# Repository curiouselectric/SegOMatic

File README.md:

# SegOMatic
Design files for a 7 segment LED DIY kit

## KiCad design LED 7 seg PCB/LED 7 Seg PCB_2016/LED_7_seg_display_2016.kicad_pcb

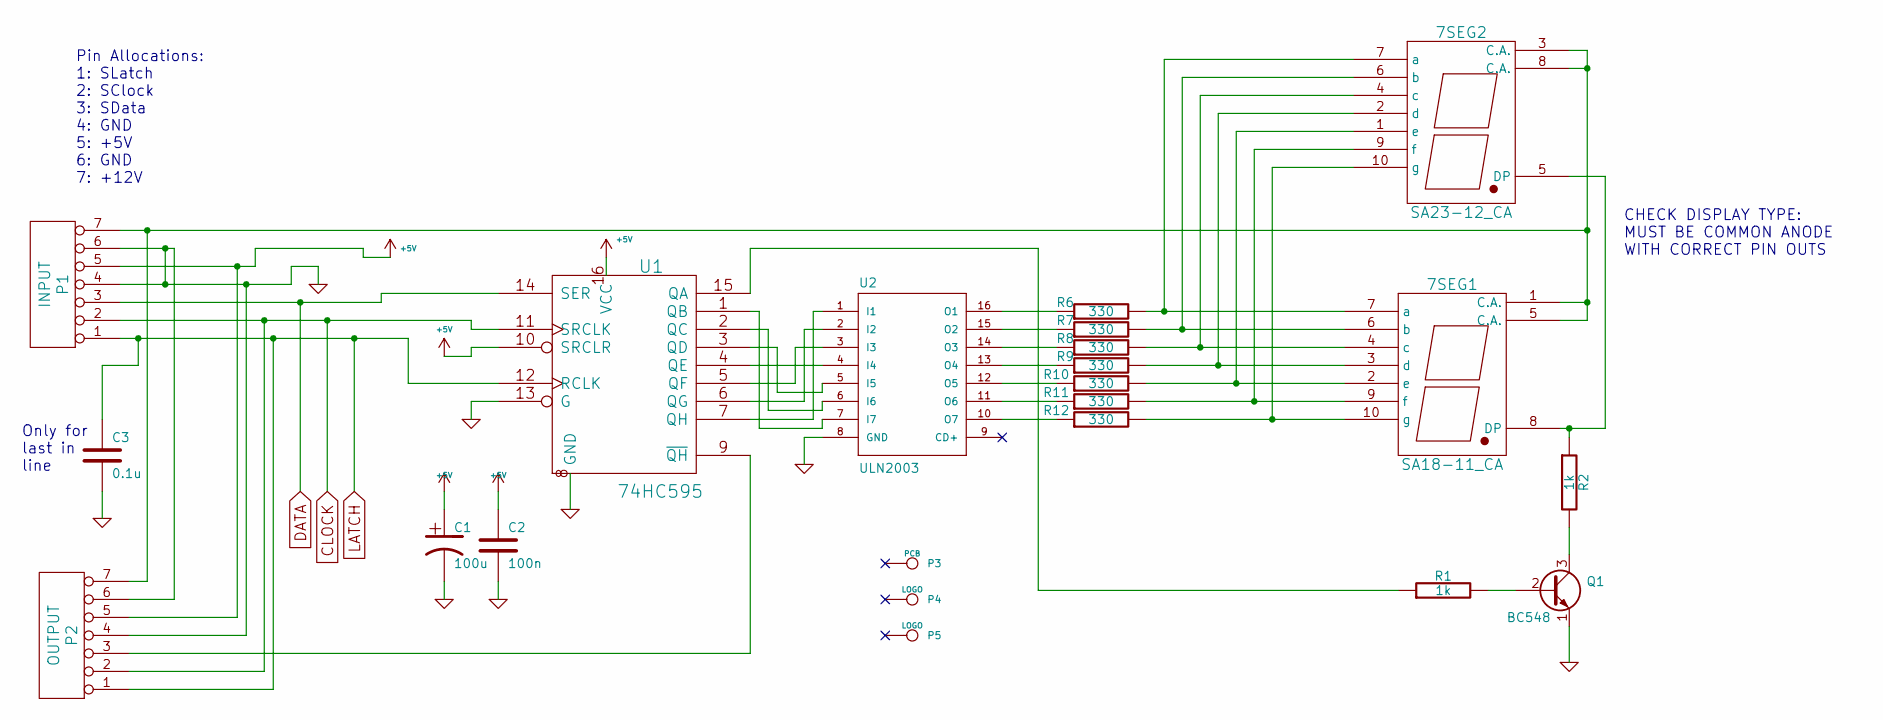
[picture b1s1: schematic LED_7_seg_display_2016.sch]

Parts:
7SEG1: SA18-11_CA; 7SEG_CA_SA18-11
7SEG2: SA23-12_CA; 7SEG_CC_2_3INCH
C1: 100u; C_Radial_D6.3_L11.2_P2.5
C2: 100n; C1_wide_lg_pad
C3: 0.1u; C1_wide_lg_pad
P1: INPUT; TH_SIL-7_large_pads
P2: OUTPUT; TH_SIL-7_large_pads
P3: PCB; PCB_40x85mm
P4: LOGO; CuriousElectric_globe_10mm
P5: LOGO; TCEC_Words_13mm
Q1: BC548; TH_TO92-EBC_large_pad
R1, R2: 1k; TH_Resistor_1
R6, R7, R8, R9, R10, R11, R12: 330; TH_Resistor_1
U1: 74HC595; TH_DIP-16__300_ELL
U2: ULN2003; TH_DIP-16__300_ELL

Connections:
+5V: C1.1, C2.1, P1.5, P2.5, U1.10 (SRCLR), U1.16 (VCC)
CLOCK: P1.2, P2.2, U1.11 (SRCLK)
DATA: P1.3, U1.14 (SER)
GND: C1.2, C2.2, C3.2, P1.4, P1.6, P2.4, P2.6, Q1.1 (E), U1.8 (GND), U1.13 (G), U2.8 (GND)
LATCH: C3.1, P1.1, P2.1, U1.12 (RCLK)
unnamed: 7SEG1.1 (C.A.), 7SEG1.5 (C.A.), 7SEG2.3 (C.A.), 7SEG2.8 (C.A.), P1.7, P2.7
unnamed: 7SEG1.2 (e), 7SEG2.1 (e), R10.2
unnamed: 7SEG1.3 (d), 7SEG2.2 (d), R9.2
unnamed: 7SEG1.4 (c), 7SEG2.4 (c), R8.2
unnamed: 7SEG1.6 (b), 7SEG2.6 (b), R7.2
unnamed: 7SEG1.7 (a), 7SEG2.7 (a), R6.2
unnamed: 7SEG1.8 (DP), 7SEG2.5 (DP), R2.1
unnamed: 7SEG1.9 (f), 7SEG2.9 (f), R11.2
unnamed: 7SEG1.10 (g), 7SEG2.10 (g), R12.2
unnamed: P2.3, U1.9 (~QH)
unnamed: Q1.2 (B), R1.2
unnamed: Q1.3 (C), R2.2
unnamed: R1.1, U1.15 (QA)
unnamed: R6.1, U2.16 (O1)
unnamed: R7.1, U2.15 (O2)
unnamed: R8.1, U2.14 (O3)
unnamed: R9.1, U2.13 (O4)
unnamed: R10.1, U2.12 (O5)
unnamed: R11.1, U2.11 (O6)
unnamed: R12.1, U2.10 (O7)
unnamed: U1.1 (QB), U2.7 (I7)
unnamed: U1.2 (QC), U2.6 (I6)
unnamed: U1.3 (QD), U2.5 (I5)
unnamed: U1.4 (QE), U2.4 (I4)
unnamed: U1.5 (QF), U2.3 (I3)
unnamed: U1.6 (QG), U2.2 (I2)
unnamed: U1.7 (QH), U2.1 (I1)

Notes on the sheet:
CHECK DISPLAY TYPE: MUST BE COMMON ANODE WITH CORRECT PIN OUTS
Pin Allocations: 1: SLatch 2: SClock 3: SData 4: GND 5: +5V 6: GND 7: +12V
Only for last in line

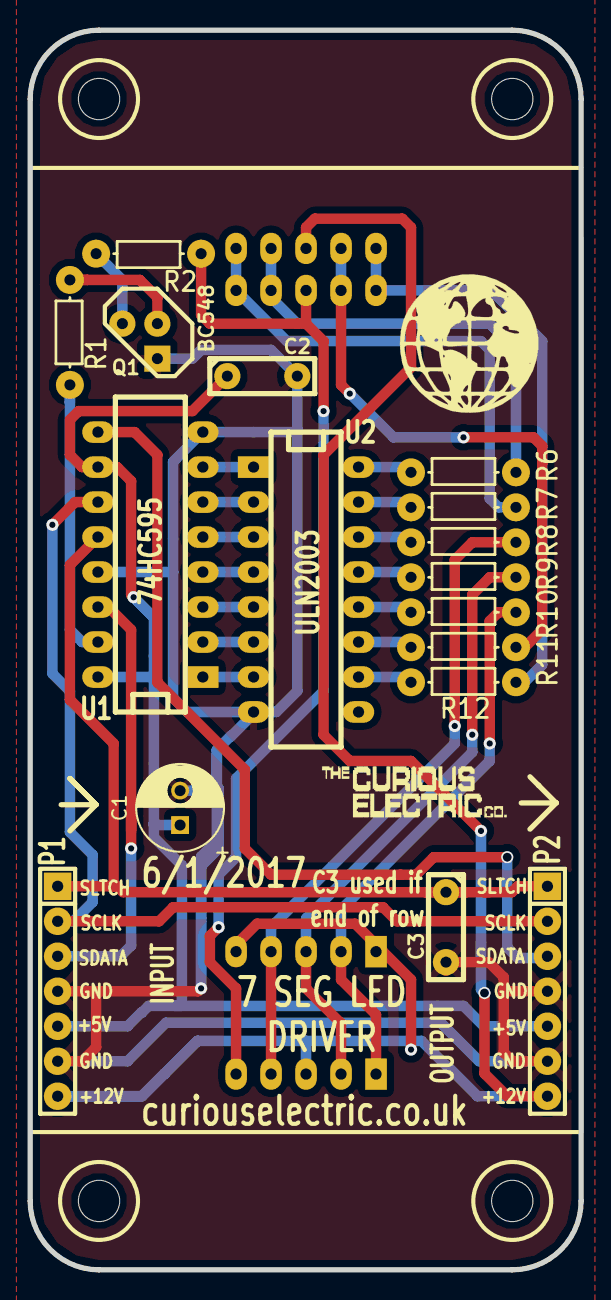
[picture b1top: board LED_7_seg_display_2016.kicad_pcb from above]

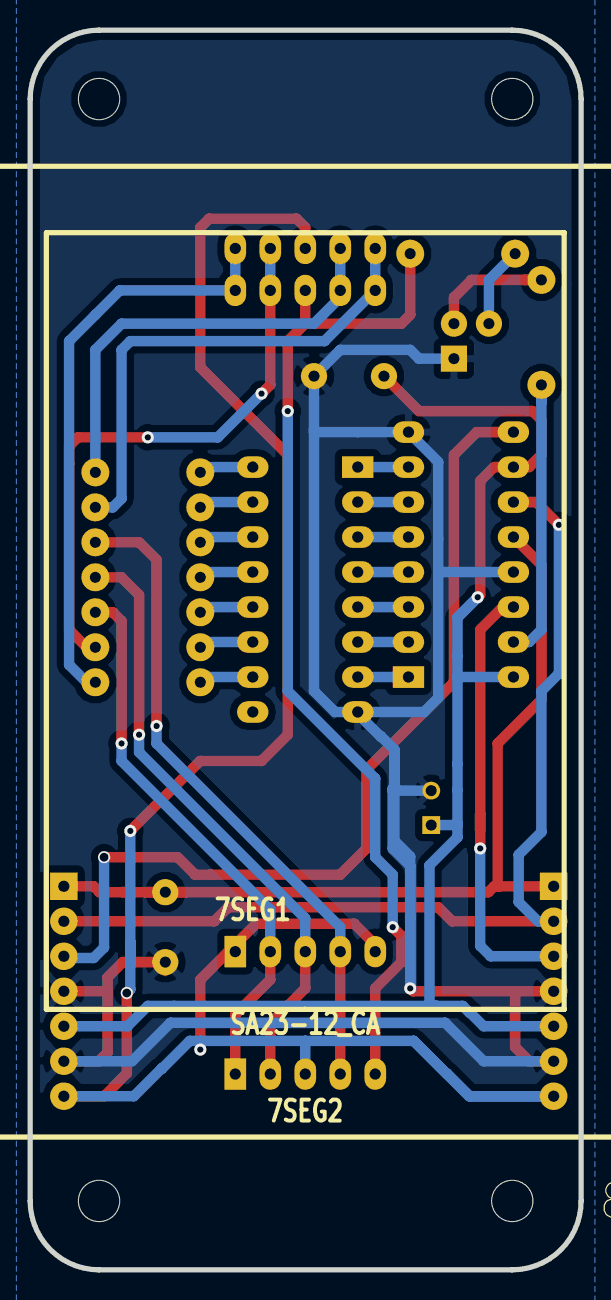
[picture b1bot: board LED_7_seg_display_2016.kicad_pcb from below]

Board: 2 copper layers, 40.0 x 90.0 mm, 22 parts (2 on the bottom side), 32 nets.

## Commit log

2015-11-30 Added Design Files and Instructions
2015-12-03 Initial files
    2015 12 3
2017-03-24 Updated new PCB design
2017-03-24 First upload of instructions
    Instructions not correct
